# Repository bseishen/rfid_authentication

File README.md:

# Overview

[Midsouth Makers](www.midsouthmakers.org) RFID access based on a [Beagle Bone Black](http://beagleboard.org/Products/BeagleBone%20Black) and a cheap Chinese wiegand reader.

# How To

## Add user
You must be a part of the administrator group to add users.

### Via the Keypad
Scan rfid token and enter your 4 digit pin.
Press the 3 key. Light will flash green and beep once completed. This will enter add user mode. Esc can be hit to exit this mode.
Scan the new RFID token, and have user enter a 4 digit pin.
Light will flash green and beep once completed successfully.

### Via the Web Interface
TODO: add content

## Delete user
You must be a part of the administrator group to add users.

### Via the Keypad
Scan rfid token and enter your 4 digit pin.
Press the 4 key. Light will flash green and beep once completed. This will enter add user mode. Esc can be hit to exit this mode.
Scan the new RFID token, and have user enter a 4 digit pin.
Light will flash green and beep once completed successfully.
Technical Details

# Source Code
All Code is located on a github repository located at: https://github.com/bseishen/rfid_authentication/

# Wiegand Reader
Reader is a 26bit Chinese special. MSB and LSB are parity bits, the remainging 24bits are the LSB of the RFID token.

Couple of gotcha's with this reader:
* Numeric key presses are sent without parity and are only 16bits.
* Buzzer lines or status led cannot be held low when trying to read data from the reader.

## Panel
## Pin Assignements
* Relay 1 - `GPIO_67` - Garage Door
* Relay 2 - `GPIO_66` - Front Door
* Relay 3 - `GPIO_44` - Buzzer
* Relay 4 - `GPIO_45` - Status LED
* Relay 5 - `GPIO_26` - UNASSIGNED
* Relay 6 - `GPIO_23` - UNASSIGNED
* Relay 7 - `GPIO_46` - UNASSIGNED
* Relay 8 - `GPIO_47` - Strobe
* `GPIO_68` - Wiegand D0
* `GPIO_69` - Wiegand D1
* `GPIO_02` - 1 wire for temperature sensor

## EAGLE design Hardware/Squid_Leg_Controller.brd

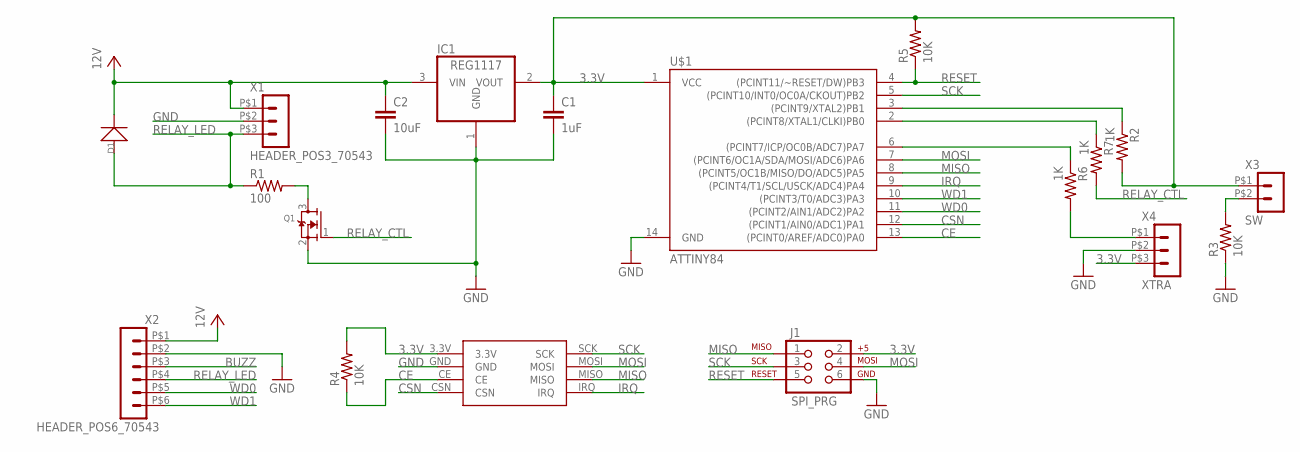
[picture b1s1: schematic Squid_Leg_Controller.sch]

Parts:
C1: 1uF; 0805
C2: 10uF; 1206
D1: D-SMA; DO-214AC
IC1: REG1117; SOT223
J1: SPI_PRG; 2X3_LOCK
Q1: MOSFET-NREFLOW; SOT23
R1: 100; R0603
R2, R6, R7: 1K; R0603
R3, R4, R5: 10K; R0603
U$1: ATTINY84; SO14
U$4: NRF24L01+; NRF24L01+_MODULE_OFFBRD
X1: HEADER_POS3_70543; 70543-POS3
X2: HEADER_POS6_70543; 70543-POS6
X3: SW; 70543-POS2
X4: XTRA; 70543-POS3

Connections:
3.3V: C1.1, IC1.2 (VOUT), J1.2, R2.2, R4.2, R5.2, U$1.1 (VCC), U$4.3.3V, X3.P$1 (1), X4.P$3 (3)
BUZZ: X2.P$3 (3)
CE: R4.1, U$1.13 ((PCINT0/AREF/ADC0)PA0), U$4.CE
CSN: U$1.12 ((PCINT1/AIN0/ADC1)PA1), U$4.CSN
GND: C1.2, C2.2, IC1.1 (GND), J1.6, Q1.2 (S), R3.1, U$1.14 (GND), U$4.GND, X1.P$2 (2), X2.P$2 (2), X4.P$2 (2)
IRQ: U$1.9 ((PCINT4/T1/SCL/USCK/ADC4)PA4), U$4.IRQ
MISO: J1.1, U$1.8 ((PCINT5/OC1B/MISO/DO/ADC5)PA5), U$4.MISO
MOSI: J1.4, U$1.7 ((PCINT6/OC1A/SDA/MOSI/ADC6)PA6), U$4.MOSI
unnamed: R2.1, U$1.3 ((PCINT9/XTAL2)PB1)
unnamed: R3.2, X3.P$2 (2)
unnamed: R6.1, U$1.6 ((PCINT7/ICP/OC0B/ADC7)PA7)
unnamed: R7.1, U$1.2 ((PCINT8/XTAL1/CLKI)PB0)
unnamed: Q1.3 (D), R1.2
unnamed: R6.2, X4.P$1 (1)
RELAY_CTL: Q1.1 (G), R7.2
RELAY_LED: D1.1 (+), R1.1, X1.P$3 (3), X2.P$4 (4)
RESET: J1.5, R5.1, U$1.4 ((PCINT11/~RESET/DW)PB3)
SCK: J1.3, U$1.5 ((PCINT10/INT0/OC0A/CKOUT)PB2), U$4.SCK
VCC: C2.1, D1.2 (-), IC1.3 (VIN), X1.P$1 (1), X2.P$1 (1)
WD0: U$1.11 ((PCINT2/AIN1/ADC2)PA2), X2.P$5 (5)
WD1: U$1.10 ((PCINT3/T0/ADC3)PA3), X2.P$6 (6)

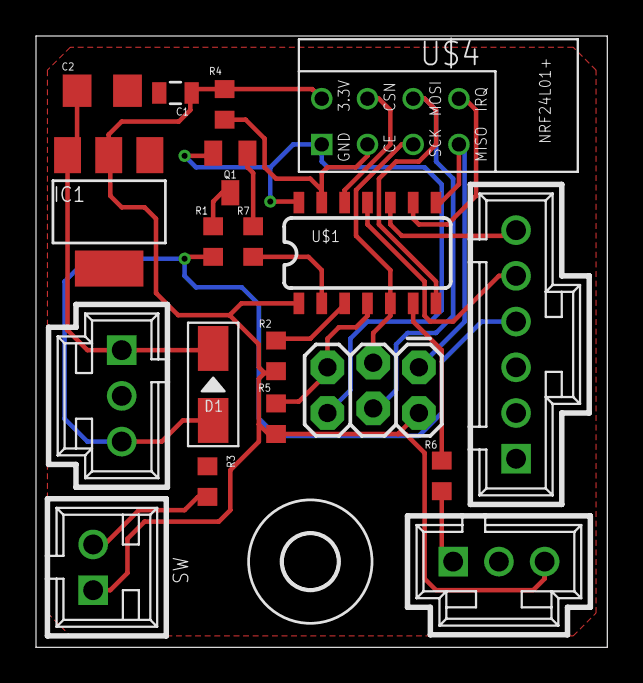
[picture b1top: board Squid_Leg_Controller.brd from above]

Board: 2 copper layers, 31.7 x 34.0 mm, 20 parts (0 on the bottom side), 20 nets.

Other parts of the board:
U$2: 3,0

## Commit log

2013-07-15 Updated the way rfid keys are stored. MSB and LSB are removed and only 24bits of the 26bit wigand is used
2013-07-16 New things to test. fixed some compile warnings.
2013-07-31 Cleaning some stuff up, changes untested.
2013-07-31 Moved DB path to config.h
2013-07-31 Added a DEFINE to add the first user to the DB
2013-08-01 Added loggin function, combines flatfile logging for webservice and syslog.
2013-08-01 Moved more defines out to the config.h
2013-08-07 adding .gitignore file. Adding binaries and .o files to gitignore, Changing sqlite location in config.h
2013-08-07 Attempt to fix broken keypad reads. .gitignore revamped
2013-08-07 Changed func log to log_err. Log is used in math.h
2013-08-07 Simplified log_err
2013-08-07 Fix Compile errors
2013-08-07 test
2013-08-07 Migrated all logging over to the new function.
2013-08-07 Changed the formatting of the log file.
2013-08-07 Changed formatting of the log file. Ctime adds a return after time stamp.
2013-08-07 Removed log err test
2013-08-07 Changed key pad functions. Esc will flush reader buffers, 3 will add a user, 4 will delete user.
2013-08-07 Added exception to flush temp buffer. Hopefully this will clear up the wiegand trash due to EMI interface from door latch.
2013-08-07 == != = Derp
2013-08-07 Included crypt.h to rfid.c
2013-08-07 All compiler warnings now cleared up. sprintf statement had to many arguments.
2013-08-07 Fixed logic issue with adding/removing users.
2013-08-07 Fixed sysloging, now using a string literal.
2013-08-07 Completed README.md, removed unessacary files thread.bak, wiegand.bak
2013-08-09 Now working, Had to fix issues with clearing the buffer after garbage was sent on the wiegand bus due to EMI
2013-08-09 Changed config
2013-08-09 Adding eclipse project file to .gitignore
2013-08-10 removing .o files
2013-08-10 Changing file open to append, not overwrite when logging
2013-08-10 Removed .o Fixed Logging bug Addd .cproject
2013-08-13 Changed time generation away from ctime to avoid the \n from ctime. Log entries should now be 1 line instead of 2
2013-08-24 Adding time to logging datestamp
2013-08-24 Adding Minutes to timestamp for logging
2013-08-24 Removing commas from datestamp
2013-09-27 Bug fix to address leading Zero's not being recognized.
2013-10-08 I <3 Markdown!
2013-11-07 Moving all software into software specific folder
2013-11-07 updating gitignore to handle new items and structure
2013-11-07 initializing hardware section
2013-11-07 adding submodules for different eagle libaries
2013-11-07 added latest DRU files from known vendors
2013-11-07 updated EagleDerp submodule with latest source
2013-11-08 saving progress on adding in buzzer and led controls
2013-11-08 routed remainig pieces, added in mosfet to control LED and buzzer, and attached DRU
2013-11-08 exported previews of current revisions
2013-11-08 added seeedstudio library
2013-11-09 updated missing resistors and removed traces on board, tracing needs to be redone
2013-11-09 updated EagleDerp with latest pull
2013-11-10 added button and rerouted board
2013-11-11 slight adjustment to board, better silk screen, changed switch to locking connector, broke out extra IO, and moved mounting hole
2013-11-11 updated previews
2014-01-17 added mac related ignores to the list

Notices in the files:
parts and their libraries:
SparkFun-DigitalIC: Licensing: CC v3.0 Share-Alike You are welcome to use this library for commercial purposes.
